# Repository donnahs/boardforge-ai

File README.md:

# BoardForge AI — HydroNode + Instrumentation Projects

Open-source PCB designs for hydroponics, environmental monitoring, and industrial instrumentation.

## Projects

| Project | Status | Description |
|---------|--------|-------------|
| HydroNode-v01 | Routed, DRC pending | 12V hydroponics controller: ESP32, 4x pump drivers, pH/EC sensors |
| DT80-IO-Exp | Planned | Serial/Modbus IO expansion board for dataTaker DT80 loggers |
| HMP155-Env | Planned | Clone of Vaisala HMP155 temperature/humidity sensor |

## License
CERN-OHL-S v2 (open hardware)

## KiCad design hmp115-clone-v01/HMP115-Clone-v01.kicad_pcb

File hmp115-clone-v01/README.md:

# HMP115 Clone v01 — Temperature + RH Probe

## Purpose
Create a practical HMP115-style humidity/temperature probe that measures **relative humidity** and **temperature** and can be used with field controllers/data loggers.

This is a **functional clone / compatible replacement direction**, not a copy of Vaisala internal hardware or firmware.

## Target behaviour
- Measure: 0–100 %RH
- Measure: temperature, target field range −40 to +60 °C for enclosure/probe use
- Power input: 5–28 V DC field supply
- Primary output: 2-wire half-duplex RS485 Modbus RTU
- Optional later outputs: 0–1 V or 0–5 V analogue temp/RH, if needed for legacy loggers
- Probe format: small PCB in vented/filter-cap enclosure with electronics protected from condensation

## v01 Architecture

```text
5–28V IN
   │
   ├─ reverse/TVS/fuse protection
   │
   ├─ buck/LDO to 3.3V
   │
   ├─ STM32C011 MCU
   │     ├─ I2C → SHT31-DIS RH/T sensor
   │     ├─ UART → MAX3485 RS485 transceiver
   │     ├─ SWD programming header
   │     └─ optional address/config pads
   │
   └─ RS485 A/B + GND + VIN connector
```

## Selected core parts

| Function | Part | LCSC | Why |
|---|---|---:|---|
| RH/T sensor | Sensirion SHT31-DIS-B2.5kS | C80862 | Factory calibrated, ±2%RH, ±0.2°C, I2C |
| MCU | STM32C011F6P6 | C5456198 | Cheap, TSSOP-20, UART/I2C, enough flash/RAM |
| RS485 | MAX3485ED-compatible | C558792 | 3.3V half-duplex RS485 |
| 3.3V regulator | AMS1117-3.3 | C6186 | easy/basic part; v02 should use lower-Iq regulator |

## Files
- `HMP115-Clone-v01.kicad_pro` — KiCad project scaffold
- `PROJECT_BRIEF.md` — product requirements
- `ELECTRICAL_DESIGN.md` — circuit architecture
- `BOM_DRAFT.csv` — draft sourcing BOM
- `FIRMWARE_SPEC.md` — firmware behaviour and Modbus map
- `ENCLOSURE_AND_CALIBRATION.md` — mechanical/filter/calibration plan
- `FIRST_BUILD_CHECKLIST.md` — what to build/test first

## Current status
v01 now has schematic capture, custom project symbols, PCB placement, autorouted copper, and a fabrication export package.

Verification:
- Schematic ERC: 0 errors, warnings only
- PCB DRC: 0 violations
- Unconnected pads: 0
- Footprint errors: 0

Important: human review is still required before ordering, especially SHT31 footprint/pin orientation, STM32 alternate-function pin mapping, field power dissipation, enclosure/filter cap, and RS485 A/B polarity.

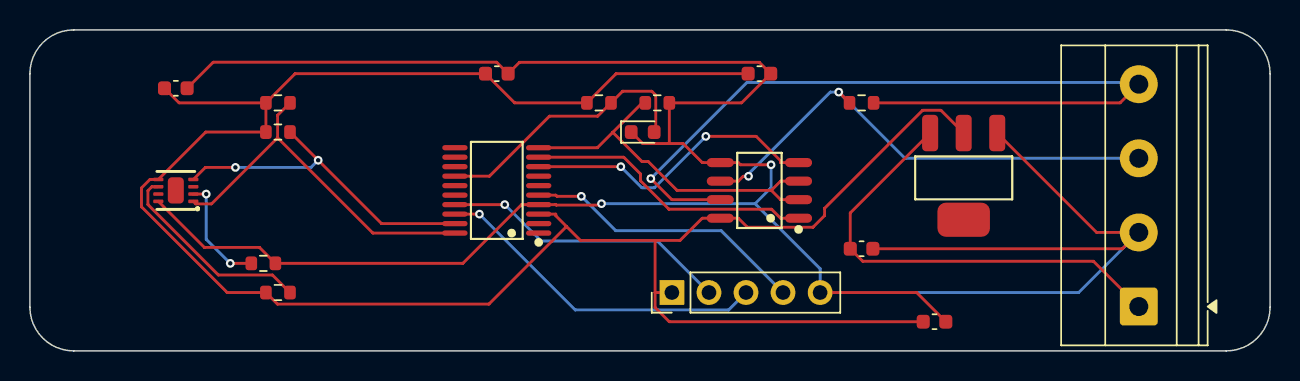
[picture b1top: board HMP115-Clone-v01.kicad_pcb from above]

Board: 2 copper layers, 85.0 x 22.0 mm, 19 parts (0 on the bottom side), 16 nets.

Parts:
C1: 10uF VIN; C_0603_1608Metric
C2: 10uF 3V3; C_0603_1608Metric
C3: 100nF MCU; C_0603_1608Metric
C4: 100nF SHT31; C_0603_1608Metric
C5: 100nF RS485; C_0603_1608Metric
D1: STATUS; LED_0603_1608Metric
J1: FIELD_5-28V_RS485; TerminalBlock_Phoenix_MKDS-1,5-4-5.08_1x04_P5.08mm_Horizont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
J2: SWD_PROG; PinHeader_1x05_P2.54mm_Vertical
R1: 4.7k SDA PU; R_0603_1608Metric
R2: 4.7k SCL PU; R_0603_1608Metric
R3: 120R TERM DNP; R_0603_1608Metric
R4: 10k DIR PD; R_0603_1608Metric
R5: 10k ADDR GND; R_0603_1608Metric
R6: 1k LED; R_0603_1608Metric
R7: 10k SHT_RESET PU; R_0603_1608Metric
U1: STM32C011F6P6; TSSOP-20_L6.5-W4.4-P0.65-LS6.4-BL
U2: SHT31-DIS-B; DFN-8_L2.5-W2.5-P0.50-BL-EP
U3: MAX3485ED; SOP-8_L4.9-W3.9-P1.27-LS6.0-BL
U4: AMS1117-3.3; SOT-223-3_L6.5-W3.4-P2.30-LS7.0-BR

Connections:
3V3: C2.1, C3.1, C4.1, C5.1, J2.1, R1.1, R2.1, R6.1, R7.1, U1.3, U2.5, U3.8, U4.2
GND: C1.2, C2.2, C3.2, C4.2, C5.2, D1.1, J1.2, J2.5, R4.2, R5.2, U1.4, U2.8, U3.5, U4.1
I2C_SCL: R2.2, U1.19, U2.4
I2C_SDA: R1.2, U1.20, U2.1
LED_DRV: D1.2, R6.2, U1.14
NRST: J2.4, U1.5
RS485_A: J1.3, R3.1, U3.6
RS485_B: J1.4, R3.2, U3.7
RS485_DI: U1.8, U3.4
RS485_DIR: R4.1, U1.10, U3.2, U3.3
RS485_RO: U1.9, U3.1
SHT_ADDR: R5.1, U2.2
SHT_RESET: R7.2, U2.6
SWCLK: J2.3, U1.18
SWDIO: J2.2, U1.17
VIN_5_28V: C1.1, J1.1, U4.3

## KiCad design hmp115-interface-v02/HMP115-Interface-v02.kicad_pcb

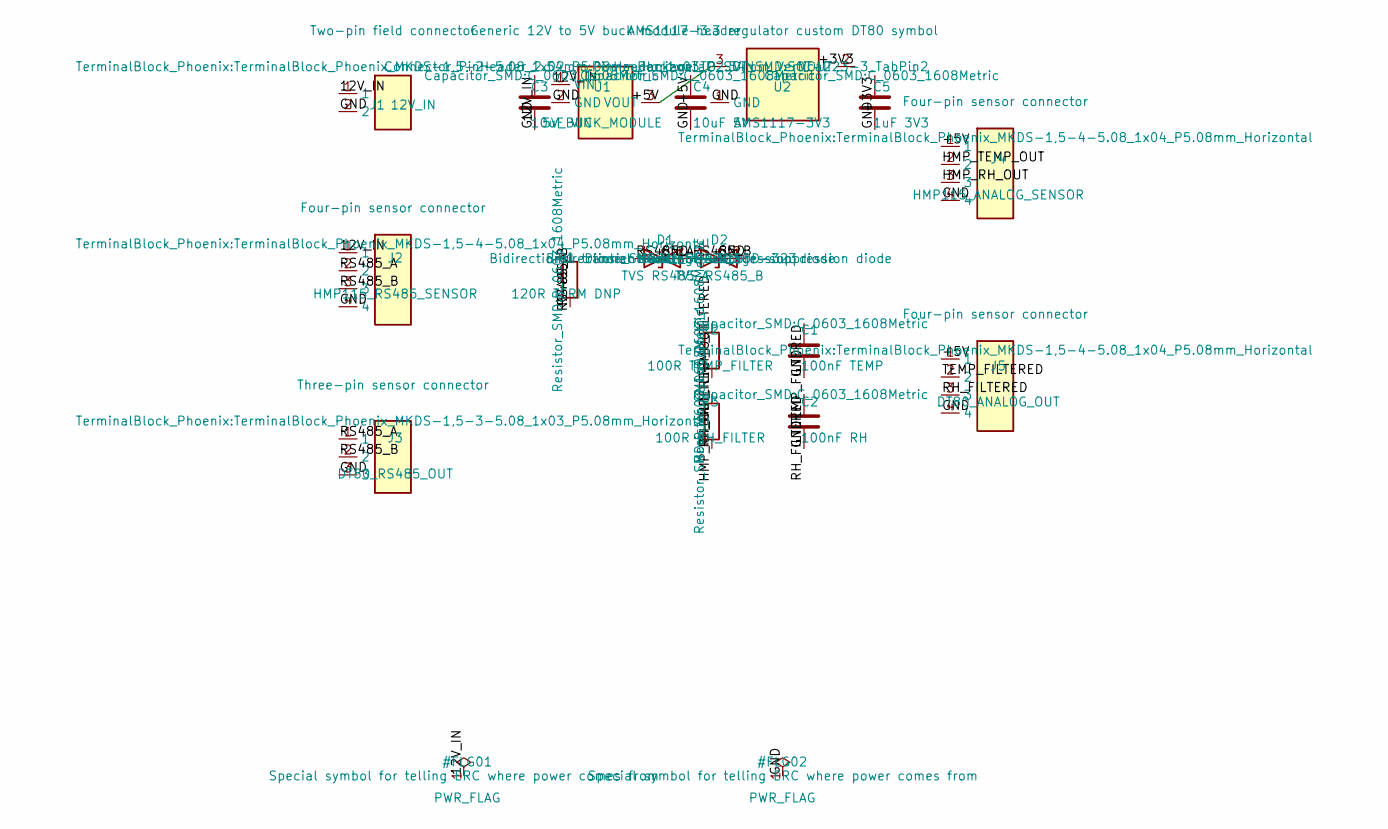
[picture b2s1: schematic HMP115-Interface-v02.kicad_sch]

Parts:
C1: 100nF TEMP; C_0603_1608Metric
C2: 100nF RH; C_0603_1608Metric
C3: 10uF VIN; C_0603_1608Metric
C4: 10uF 5V; C_0603_1608Metric
C5: 1uF 3V3; C_0603_1608Metric
D1: TVS RS485_A; D_SOD-323
D2: TVS RS485_B; D_SOD-323
J1: 12V_IN; TerminalBlock_Phoenix_MKDS-1,5-2-5.08_1x02_P5.08mm_Horizont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
J2: HMP115_RS485_SENSOR; TerminalBlock_Phoenix_MKDS-1,5-4-5.08_1x04_P5.08mm_Horizont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
J3: DT80_RS485_OUT; TerminalBlock_Phoenix_MKDS-1,5-3-5.08_1x03_P5.08mm_Horizont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
J4: HMP115_ANALOG_SENSOR; TerminalBlock_Phoenix_MKDS-1,5-4-5.08_1x04_P5.08mm_Horizont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
J5: DT80_ANALOG_OUT; TerminalBlock_Phoenix_MKDS-1,5-4-5.08_1x04_P5.08mm_Horizont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
R1: 120R TERM DNP; R_0603_1608Metric
R2: 100R TEMP_FILTER; R_0603_1608Metric
R3: 100R RH_FILTER; R_0603_1608Metric
U1: 5V_BUCK_MODULE; PinHeader_1x03_P2.54mm_Vertical
U2: AMS1117-3V3; SOT-223-3_TabPin2

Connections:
12V_IN: C3.1, J1.1, J2.1, U1.1 (VIN)
+3V3: C5.1, U2.2 (VOUT)
+5V: C4.1, J4.1, J5.1, U1.3 (VOUT), U2.3 (VIN)
GND: C1.2, C2.2, C3.2, C4.2, C5.2, D1.2 (A2), D2.2 (A2), J1.2, J2.4, J3.3, J4.4, J5.4, U1.2 (GND), U2.1 (GND)
HMP_RH_OUT: J4.3, R3.1
HMP_TEMP_OUT: J4.2, R2.1
RH_FILTERED: C2.1, J5.3, R3.2
RS485_A: D1.1 (A1), J2.2, J3.1, R1.1
RS485_B: D2.1 (A1), J2.3, J3.2, R1.2
TEMP_FILTERED: C1.1, J5.2, R2.2

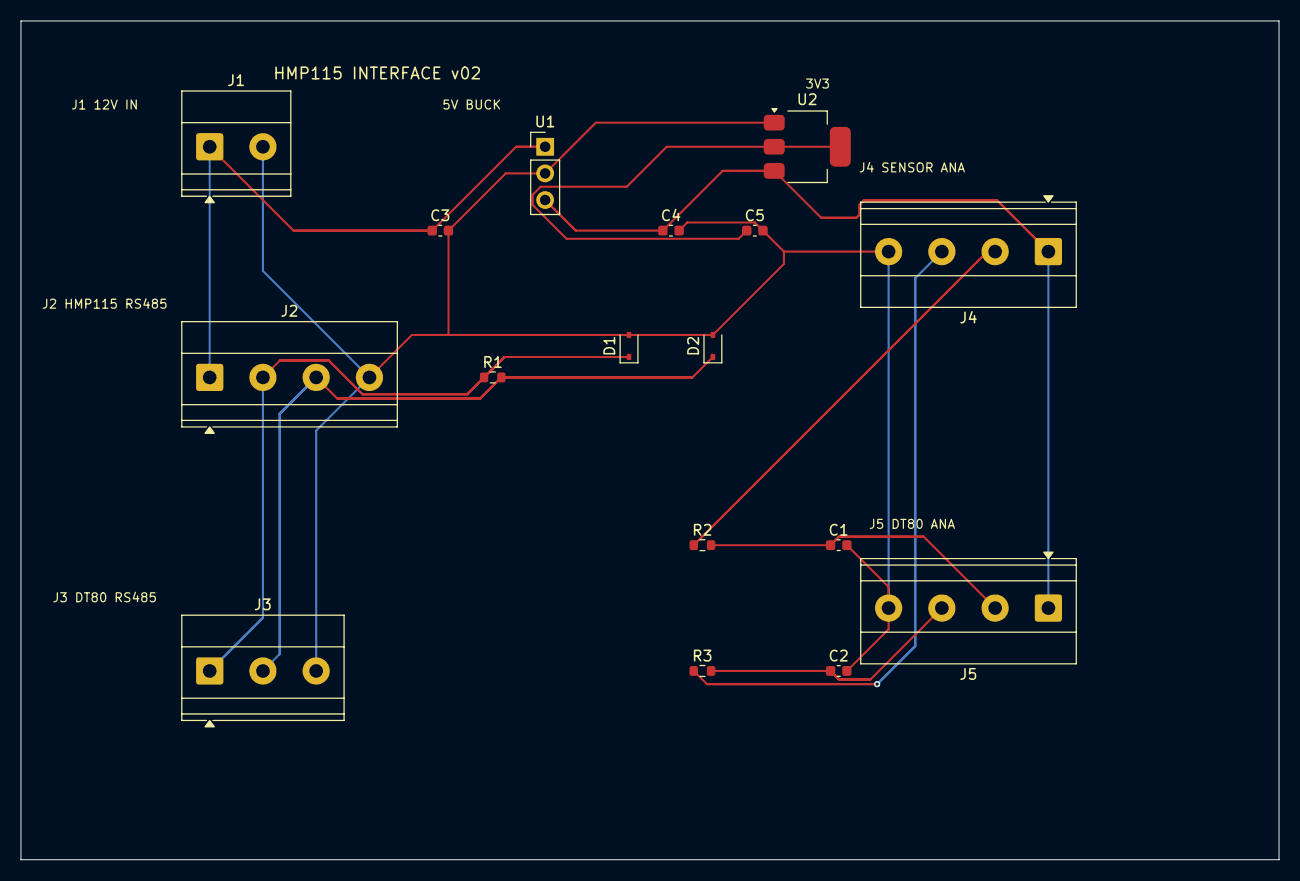
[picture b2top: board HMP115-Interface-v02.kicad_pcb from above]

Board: 2 copper layers, 120.0 x 80.0 mm, 17 parts (0 on the bottom side), 10 nets.

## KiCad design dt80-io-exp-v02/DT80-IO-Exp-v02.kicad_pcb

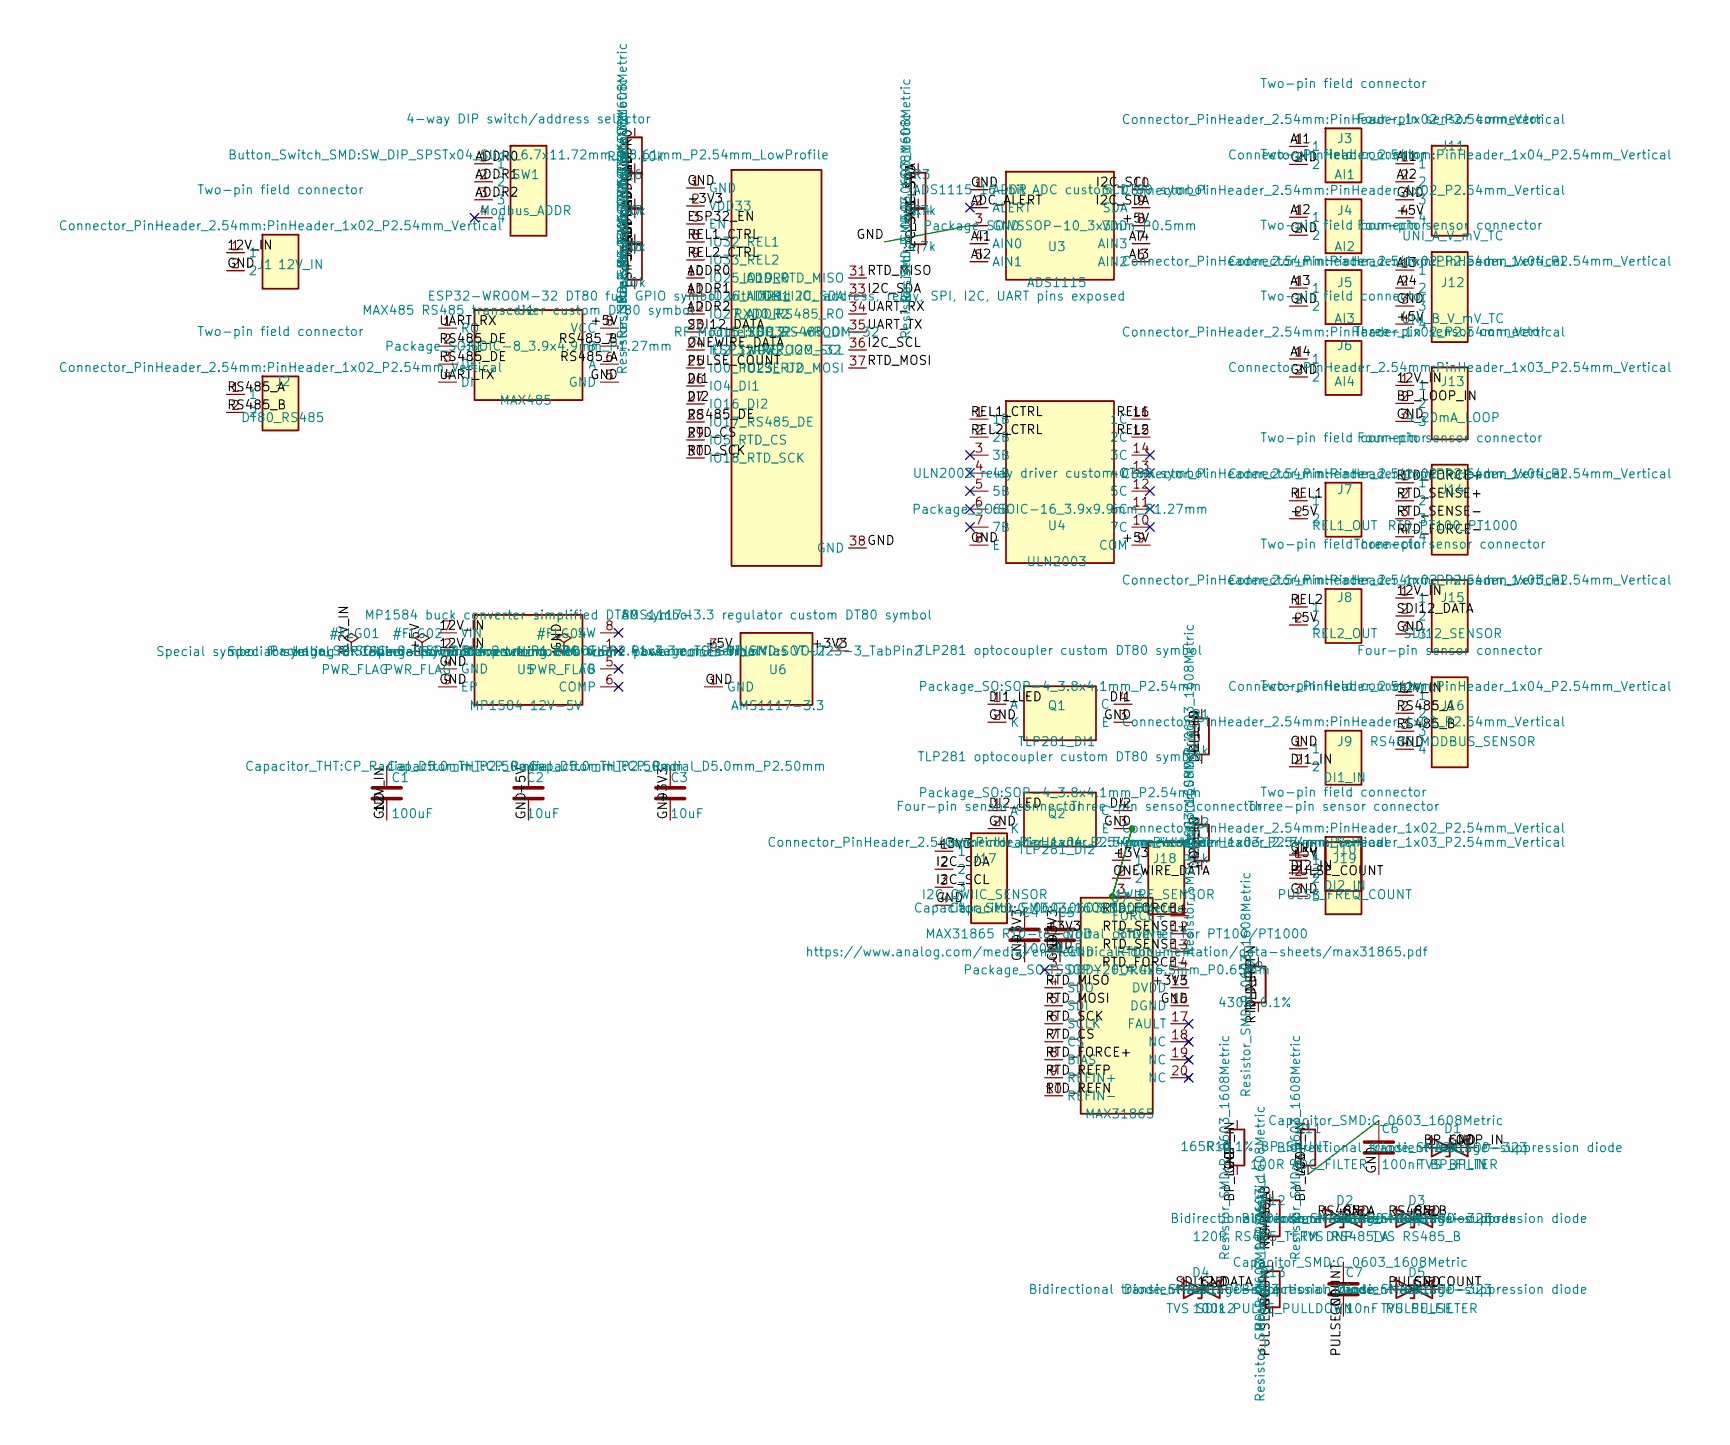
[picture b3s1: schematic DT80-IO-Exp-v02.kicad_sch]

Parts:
C1: 100uF; CP_Radial_D5.0mm_P2.50mm
C2, C3: 10uF; CP_Radial_D5.0mm_P2.50mm
C4: 100nF; C_0603_1608Metric
C5: 1uF; C_0603_1608Metric
C6: 100nF BP_FILTER; C_0603_1608Metric
C7: 10nF PULSE_FILTER; C_0603_1608Metric
D1: TVS BP_IN; D_SOD-323
D2: TVS RS485_A; D_SOD-323
D3: TVS RS485_B; D_SOD-323
D4: TVS SDI12; D_SOD-323
D5: TVS PULSE; D_SOD-323
J1: 12V_IN; PinHeader_1x02_P2.54mm_Vertical
J2: DT80_RS485; PinHeader_1x02_P2.54mm_Vertical
J3: AI1; PinHeader_1x02_P2.54mm_Vertical
J4: AI2; PinHeader_1x02_P2.54mm_Vertical
J5: AI3; PinHeader_1x02_P2.54mm_Vertical
J6: AI4; PinHeader_1x02_P2.54mm_Vertical
J7: REL1_OUT; PinHeader_1x02_P2.54mm_Vertical
J8: REL2_OUT; PinHeader_1x02_P2.54mm_Vertical
J9: DI1_IN; PinHeader_1x02_P2.54mm_Vertical
J10: DI2_IN; PinHeader_1x02_P2.54mm_Vertical
J11: UNI_A_V_mV_TC; PinHeader_1x04_P2.54mm_Vertical
J12: UNI_B_V_mV_TC; PinHeader_1x04_P2.54mm_Vertical
J13: 4_20mA_LOOP; PinHeader_1x03_P2.54mm_Vertical
J14: RTD_PT100_PT1000; PinHeader_1x04_P2.54mm_Vertical
J15: SDI12_SENSOR; PinHeader_1x03_P2.54mm_Vertical
J16: RS485_MODBUS_SENSOR; PinHeader_1x04_P2.54mm_Vertical
J17: I2C_QWIIC_SENSOR; PinHeader_1x04_P2.54mm_Vertical
J18: 1WIRE_SENSOR; PinHeader_1x03_P2.54mm_Vertical
J19: PULSE_FREQ_COUNT; PinHeader_1x03_P2.54mm_Vertical
Q1: TLP281_DI1; SOP-4_3.8x4.1mm_P2.54mm
Q2: TLP281_DI2; SOP-4_3.8x4.1mm_P2.54mm
R1, R2: 1k; R_0603_1608Metric
R3, R4: 4.7k; R_0603_1608Metric
R5, R6, R7, R8: 10k; R_0603_1608Metric
R9: 430R 0.1%; R_0603_1608Metric
R10: 165R 0.1% BP_SHUNT; R_0603_1608Metric
R11: 100R ADC_FILTER; R_0603_1608Metric
R12: 120R RS485_TERM DNP; R_0603_1608Metric
R13: 100k PULSE_PULLDOWN; R_0603_1608Metric
SW1: Modbus_ADDR; SW_DIP_SPSTx04_Slide_6.7x11.72mm_W8.61mm_P2.54mm_LowProfile
U1: MAX485; SOIC-8_3.9x4.9mm_P1.27mm
U2: ESP32-WROOM-32
U3: ADS1115; VSSOP-10_3x3mm_P0.5mm
U4: ULN2003; SOIC-16_3.9x9.9mm_P1.27mm
U5: MP1584 12V-5V; SOIC-8-1EP_3.9x4.9mm_P1.27mm_EP2.41x3.3mm_ThermalVias
U6: AMS1117-3.3; SOT-223-3_TabPin2
U7: MAX31865; TSSOP-20_4.4x6.5mm_P0.65mm

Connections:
12V_IN: C1.1, J1.1, J13.1, J15.1, J16.1, U5.2 (EN), U5.7 (VIN)
+3V3: C3.1, C4.1, C5.1, J17.1, J18.1, R3.1, R4.1, R8.1, U2.2 (VDD33), U6.2 (VOUT), U7.1 (VDD), U7.15 (DVDD)
+5V: C2.1, J7.2, J8.2, J11.4, J12.4, J19.1, U1.8 (VCC), U3.8 (VDD), U4.9 (COM), U6.3 (VIN)
ADC_ALERT: U3.2 (ALERT)
ADDR0: R5.1, SW1.1, U2.10 (IO25_ADDR0)
ADDR1: R6.1, SW1.2, U2.11 (IO26_ADDR1)
ADDR2: R7.1, SW1.3, U2.12 (IO27_ADDR2)
AI1: J3.1, J11.1, U3.4 (AIN0)
AI2: J4.1, J11.2, U3.5 (AIN1)
AI3: C6.1, J5.1, J12.1, R11.2, U3.6 (AIN2)
AI4: J6.1, J12.2, U3.7 (AIN3)
BP_LOOP_IN: D1.1 (A1), J13.2, R10.1, R11.1
DI1: Q1.4 (C), U2.26 (IO4_DI1)
DI1_IN: J9.2, R1.1
DI1_LED: Q1.1 (A), R1.2
DI2: Q2.4 (C), U2.27 (IO16_DI2)
DI2_IN: J10.2, R2.1
DI2_LED: Q2.1 (A), R2.2
ESP32_EN: R8.2, U2.3 (EN)
GND: C1.2, C2.2, C3.2, C4.2, C5.2, C6.2, C7.2, D1.2 (A2), D2.2 (A2), D3.2 (A2), D4.2 (A2), D5.2 (A2), J1.2, J3.2, J4.2, J5.2, J6.2, J9.1, J10.1, J11.3, J12.3, J13.3, J15.3, J16.4, J17.4, J18.3, J19.3, Q1.2 (K), Q1.3 (E), Q2.2 (K), Q2.3 (E), R5.2, R6.2, R7.2, R10.2, R13.2, U1.5 (GND), U2.1 (GND), U2.38 (GND), U3.1 (ADDR), U3.3 (GND), U4.8 (E), U5.4 (GND), U5.9 (EP), U6.1 (GND), U7.2 (GND), U7.16 (DGND)
I2C_SCL: J17.3, R4.2, U2.36 (IO22_I2C_SCL), U3.10 (SCL)
I2C_SDA: J17.2, R3.2, U2.33 (IO21_I2C_SDA), U3.9 (SDA)
ONEWIRE_DATA: J18.2, U2.24 (IO2_1WIRE)
PULSE_COUNT: C7.1, D5.1 (A1), J19.2, R13.1, U2.25 (IO0_PULSE)
REL1: J7.1, U4.16 (1C)
REL1_CTRL: U2.8 (IO32_REL1), U4.1 (1B)
REL2: J8.1, U4.15 (2C)
REL2_CTRL: U2.9 (IO33_REL2), U4.2 (2B)
RS485_A: D2.1 (A1), J2.1, J16.2, R12.1, U1.6 (A)
RS485_B: D3.1 (A1), J2.2, J16.3, R12.2, U1.7 (B)
RS485_DE: U1.2 (~RE), U1.3 (DE), U2.28 (IO17_RS485_DE)
RTD_CS: U2.29 (IO5_RTD_CS), U7.7 (CS)
RTD_FORCE+: J14.1, U7.8 (BIAS), U7.11 (FORCE+)
RTD_FORCE-: J14.4, U7.14 (FORCE-)
RTD_MISO: U2.31 (IO19_RTD_MISO), U7.4 (SDO)
RTD_MOSI: U2.37 (IO23_RTD_MOSI), U7.5 (SDI)
RTD_REFN: R9.2, U7.10 (REFIN-)
RTD_REFP: R9.1, U7.9 (REFIN+)
RTD_SCK: U2.30 (IO18_RTD_SCK), U7.6 (SCLK)
RTD_SENSE+: J14.2, U7.12 (RTDIN+)
RTD_SENSE-: J14.3, U7.13 (RTDIN-)
SDI12_DATA: D4.1 (A1), J15.2, U2.23 (IO15_SDI12)
UART_RX: U1.1 (RO), U2.34 (RXD0_RS485_RO)
UART_TX: U1.4 (DI), U2.35 (TXD0_RS485_DI)

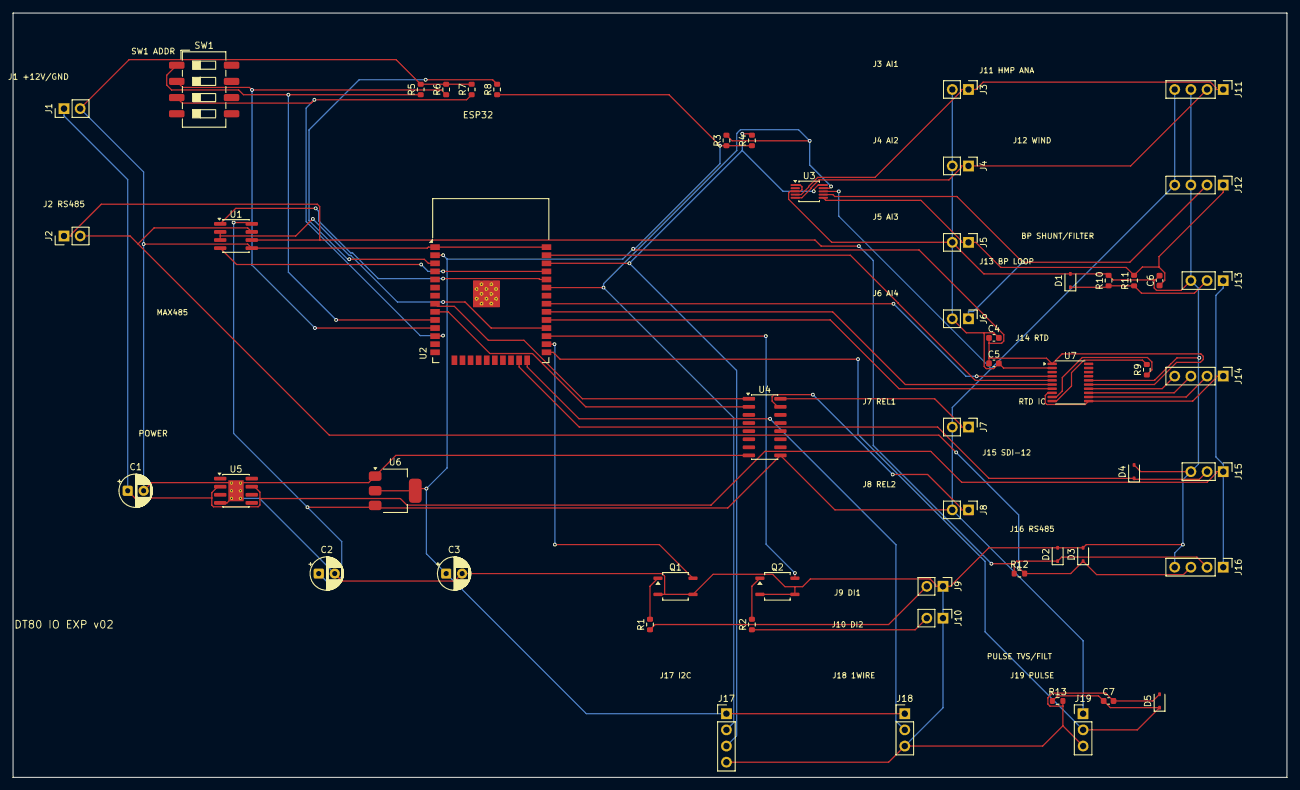
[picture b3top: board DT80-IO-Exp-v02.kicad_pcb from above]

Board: 2 copper layers, 200.0 x 120.0 mm, 54 parts (0 on the bottom side), 43 nets.

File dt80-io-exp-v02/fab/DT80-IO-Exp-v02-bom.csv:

"Reference","Value","Footprint","Datasheet"
"C1","100uF","Capacitor_THT:CP_Radial_D5.0mm_P2.50mm",""
"C2","10uF","Capacitor_THT:CP_Radial_D5.0mm_P2.50mm",""
"C3","10uF","Capacitor_THT:CP_Radial_D5.0mm_P2.50mm",""
"C4","100nF","Capacitor_SMD:C_0603_1608Metric",""
"C5","1uF","Capacitor_SMD:C_0603_1608Metric",""
"C6","100nF BP_FILTER","Capacitor_SMD:C_0603_1608Metric",""
"C7","10nF PULSE_FILTER","Capacitor_SMD:C_0603_1608Metric",""
"D1","TVS BP_IN","Diode_SMD:D_SOD-323",""
"D2","TVS RS485_A","Diode_SMD:D_SOD-323",""
"D3","TVS RS485_B","Diode_SMD:D_SOD-323",""
"D4","TVS SDI12","Diode_SMD:D_SOD-323",""
"D5","TVS PULSE","Diode_SMD:D_SOD-323",""
"J1","12V_IN","Connector_PinHeader_2.54mm:PinHeader_1x02_P2.54mm_Vertical",""
"J2","DT80_RS485","Connector_PinHeader_2.54mm:PinHeader_1x02_P2.54mm_Vertical",""
"J3","AI1","Connector_PinHeader_2.54mm:PinHeader_1x02_P2.54mm_Vertical",""
"J4","AI2","Connector_PinHeader_2.54mm:PinHeader_1x02_P2.54mm_Vertical",""
"J5","AI3","Connector_PinHeader_2.54mm:PinHeader_1x02_P2.54mm_Vertical",""
"J6","AI4","Connector_PinHeader_2.54mm:PinHeader_1x02_P2.54mm_Vertical",""
"J7","REL1_OUT","Connector_PinHeader_2.54mm:PinHeader_1x02_P2.54mm_Vertical",""
"J8","REL2_OUT","Connector_PinHeader_2.54mm:PinHeader_1x02_P2.54mm_Vertical",""
"J9","DI1_IN","Connector_PinHeader_2.54mm:PinHeader_1x02_P2.54mm_Vertical",""
"J10","DI2_IN","Connector_PinHeader_2.54mm:PinHeader_1x02_P2.54mm_Vertical",""
"J11","UNI_A_V_mV_TC","Connector_PinHeader_2.54mm:PinHeader_1x04_P2.54mm_Vertical",""
"J12","UNI_B_V_mV_TC","Connector_PinHeader_2.54mm:PinHeader_1x04_P2.54mm_Vertical",""
"J13","4_20mA_LOOP","Connector_PinHeader_2.54mm:PinHeader_1x03_P2.54mm_Vertical",""
"J14","RTD_PT100_PT1000","Connector_PinHeader_2.54mm:PinHeader_1x04_P2.54mm_Vertical",""
"J15","SDI12_SENSOR","Connector_PinHeader_2.54mm:PinHeader_1x03_P2.54mm_Vertical",""
"J16","RS485_MODBUS_SENSOR","Connector_PinHeader_2.54mm:PinHeader_1x04_P2.54mm_Vertical",""
"J17","I2C_QWIIC_SENSOR","Connector_PinHeader_2.54mm:PinHeader_1x04_P2.54mm_Vertical",""
"J18","1WIRE_SENSOR","Connector_PinHeader_2.54mm:PinHeader_1x03_P2.54mm_Vertical",""
"J19","PULSE_FREQ_COUNT","Connector_PinHeader_2.54mm:PinHeader_1x03_P2.54mm_Vertical",""
"Q1","TLP281_DI1","Package_SO:SOP-4_3.8x4.1mm_P2.54mm",""
"Q2","TLP281_DI2","Package_SO:SOP-4_3.8x4.1mm_P2.54mm",""
"R1","1k","Resistor_SMD:R_0603_1608Metric",""
"R2","1k","Resistor_SMD:R_0603_1608Metric",""
"R3","4.7k","Resistor_SMD:R_0603_1608Metric",""
"R4","4.7k","Resistor_SMD:R_0603_1608Metric",""
"R5","10k","Resistor_SMD:R_0603_1608Metric",""
"R6","10k","Resistor_SMD:R_0603_1608Metric",""
"R7","10k","Resistor_SMD:R_0603_1608Metric",""
"R8","10k","Resistor_SMD:R_0603_1608Metric",""
"R9","430R 0.1%","Resistor_SMD:R_0603_1608Metric",""
"R10","165R 0.1% BP_SHUNT","Resistor_SMD:R_0603_1608Metric",""
"R11","100R ADC_FILTER","Resistor_SMD:R_0603_1608Metric",""
"R12","120R RS485_TERM DNP","Resistor_SMD:R_0603_1608Metric",""
"R13","100k PULSE_PULLDOWN","Resistor_SMD:R_0603_1608Metric",""
"SW1","Modbus_ADDR","Button_Switch_SMD:SW_DIP_SPSTx04_Slide_6.7x11.72mm_W8.61mm_P2.54mm_LowProfile",""
"U1","MAX485","Package_SO:SOIC-8_3.9x4.9mm_P1.27mm",""
"U2","ESP32-WROOM-32","RF_Module:ESP32-WROOM-32",""
"U3","ADS1115","Package_SO:VSSOP-10_3x3mm_P0.5mm",""
"U4","ULN2003","Package_SO:SOIC-16_3.9x9.9mm_P1.27mm",""
"U5","MP1584 12V-5V","Package_SO:SOIC-8-1EP_3.9x4.9mm_P1.27mm_EP2.41x3.3mm_ThermalVias",""
"U6","AMS1117-3.3","Package_TO_SOT_SMD:SOT-223-3_TabPin2",""
"U7","MAX31865","Package_SO:TSSOP-20_4.4x6.5mm_P0.65mm","https://www.analog.com/media/en/technical-documentation/data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"
